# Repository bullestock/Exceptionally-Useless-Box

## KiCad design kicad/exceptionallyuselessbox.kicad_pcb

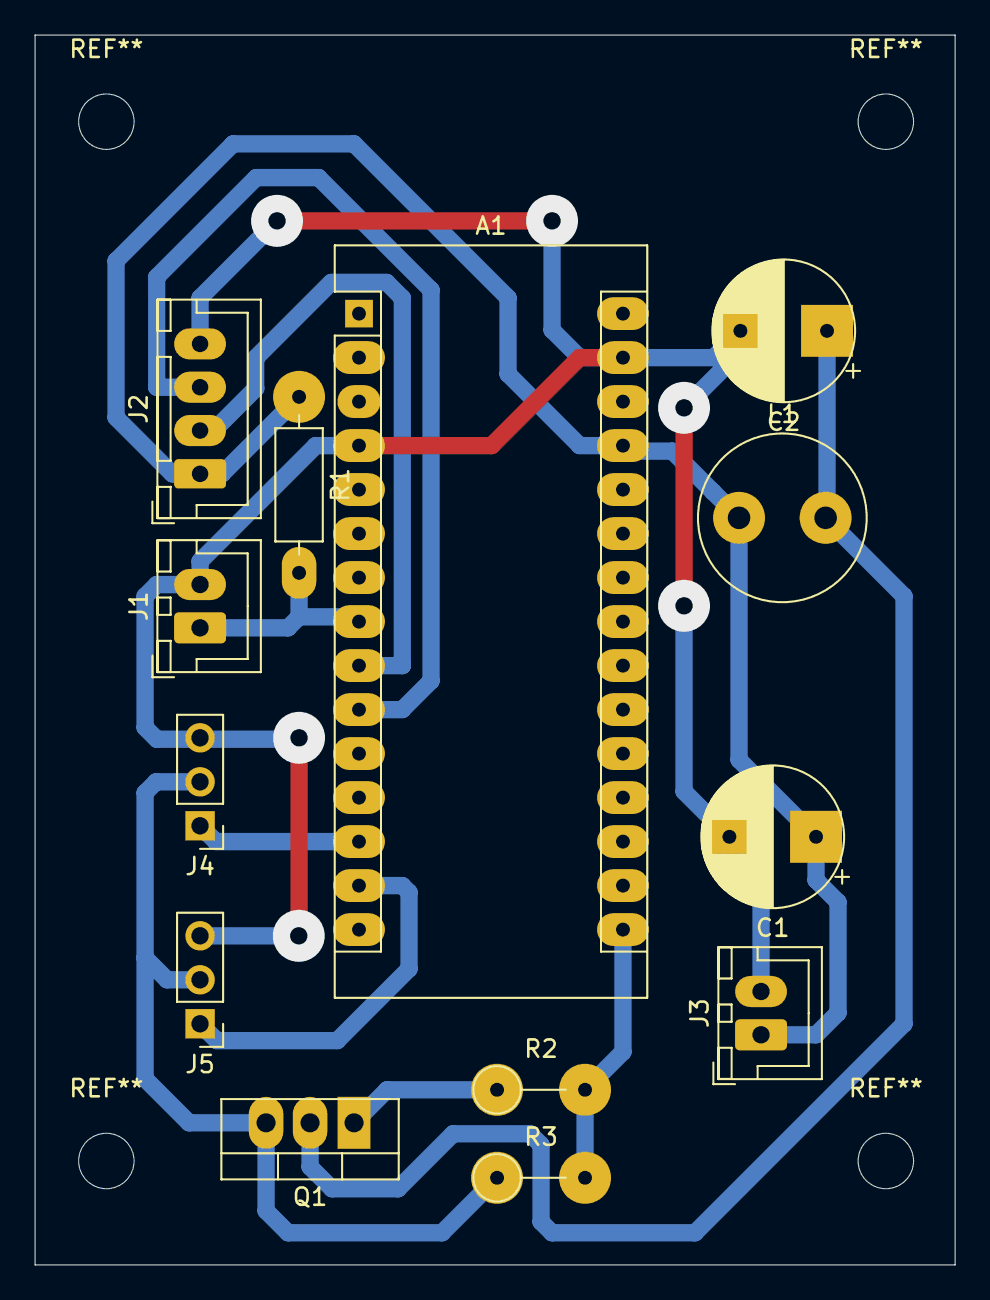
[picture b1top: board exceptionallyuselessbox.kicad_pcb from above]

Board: 2 copper layers, 53.1 x 71.0 mm, 13 parts (0 on the bottom side), 11 nets.

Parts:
A1: Arduino_Nano_v3.x; Arduino_Nano
C1, C2: 100u; CP_Radial_D8.0mm_P5.00mm
J1, J3: Conn_01x02; JST_XH_B02B-XH-A_1x02_P2.50mm_Vertical
J2: Conn_01x04; JST_XH_B04B-XH-A_1x04_P2.50mm_Vertical
J4, J5: Conn_01x03; PinHeader_1x03_P2.54mm_Vertical
L1: 10 mH; L_Radial_D9.5mm_P5.00mm_Fastron_07HVP
Q1: IRFZ44N; TO-220-3_Vertical
R1: 10k; R_Axial_DIN0207_L6.3mm_D2.5mm_P10.16mm_Horizontal
R2: 1K; R_Axial_DIN0207_L6.3mm_D2.5mm_P5.08mm_Vertical
R3: 10K; R_Axial_DIN0207_L6.3mm_D2.5mm_P5.08mm_Vertical

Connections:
+5V: A1.27, C1.1, J2.1, J3.1, L1.1, R1.1
BOT: A1.14, J5.1
GND: A1.4, A1.29, C1.2, C2.2, J1.2, J2.4, J3.2, J4.3, J5.3
unnamed: A1.8, J1.1, R1.2
unnamed: A1.9, J2.2
unnamed: A1.10, J2.3
unnamed: C2.1, L1.2, Q1.2
unnamed: J4.2, J5.2, Q1.3, R3.1
unnamed: Q1.1, R2.1
SERVO_ON: A1.16, R2.2, R3.2
TOP: A1.13, J4.1

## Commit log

2019-06-30 Add SVGs for Lasersaur.
2019-06-30 Add diagram.
2019-07-05 Break apart and recombine.
2019-07-05 Add viewbox.
2019-07-05 Make usable.
2019-07-05 Fix grouping.
2019-07-05 Complete PCB.
2019-07-06 Fix servo pinout.
2019-07-06 Redraw linkage parts to get correct paths.
2019-07-06 Convert linkage SVGs to STL.
2019-07-29 Add servo adapter.
2019-07-29 Remove unneeded holes.
2019-07-31 Regenerate.
2019-07-31 Regenerate STL files.
2019-07-31 Update-
2019-07-31 Add.
2019-07-31 Cleanup.
2019-08-01 Add hammer.
2019-08-01 Reduce length.
2019-08-01 Rotate servo slot.
2019-08-03 Rotate slot.
2019-08-16 Rename .ino file-.
2019-08-21 Try to work around crappy sensor.
2019-08-31 Tweak 3D-printed parts.
2019-08-31 Update PCB.
2019-08-31 Use I2C sensor.
2019-09-01 Front plate for TOF10120 sensor.
